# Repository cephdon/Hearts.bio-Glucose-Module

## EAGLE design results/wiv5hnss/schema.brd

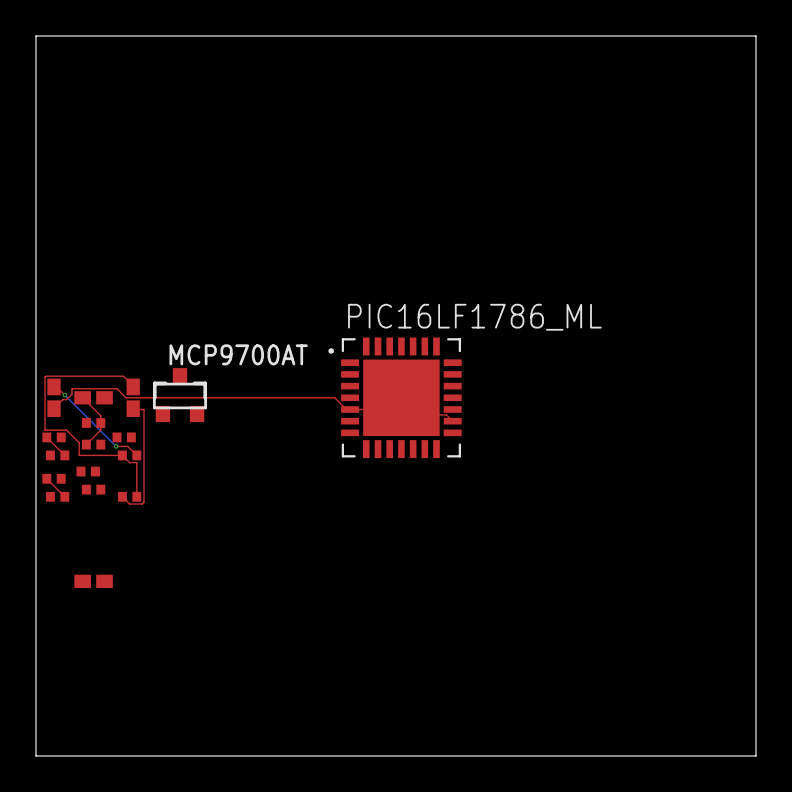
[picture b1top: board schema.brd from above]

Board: 2 copper layers, 40.0 x 40.0 mm, 17 parts (0 on the bottom side), 7 nets.

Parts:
C79, C80, C91, C183: C_0402_10U_6V3; C_0402
MCP9700AT: MCP9700SMD; SOT23-3
PIC16LF1786_ML: PIC16LF1786; 28-QFN
R49, R50, R81, R82, R85, R86, R87, R88, R89, R90, R94: R_0402_1R0; R_0402

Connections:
unnamed: C79.1, R50.P$1
unnamed: C79.2, R49.P$1, R50.P$2
unnamed: C80.1, PIC16LF1786_ML.P$5, PIC16LF1786_ML.P$16, PIC16LF1786_ML.PAD
unnamed: C80.2, R49.P$2
unnamed: C91.1, R87.P$2, R88.P$1
unnamed: R81.P$1, R85.P$2
unnamed: R82.P$1, R86.P$2

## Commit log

2015-04-13 CT-62. Modeled the glucose block of Joseph Kim's glucose design. Ignored Spiral 1 part of design.
